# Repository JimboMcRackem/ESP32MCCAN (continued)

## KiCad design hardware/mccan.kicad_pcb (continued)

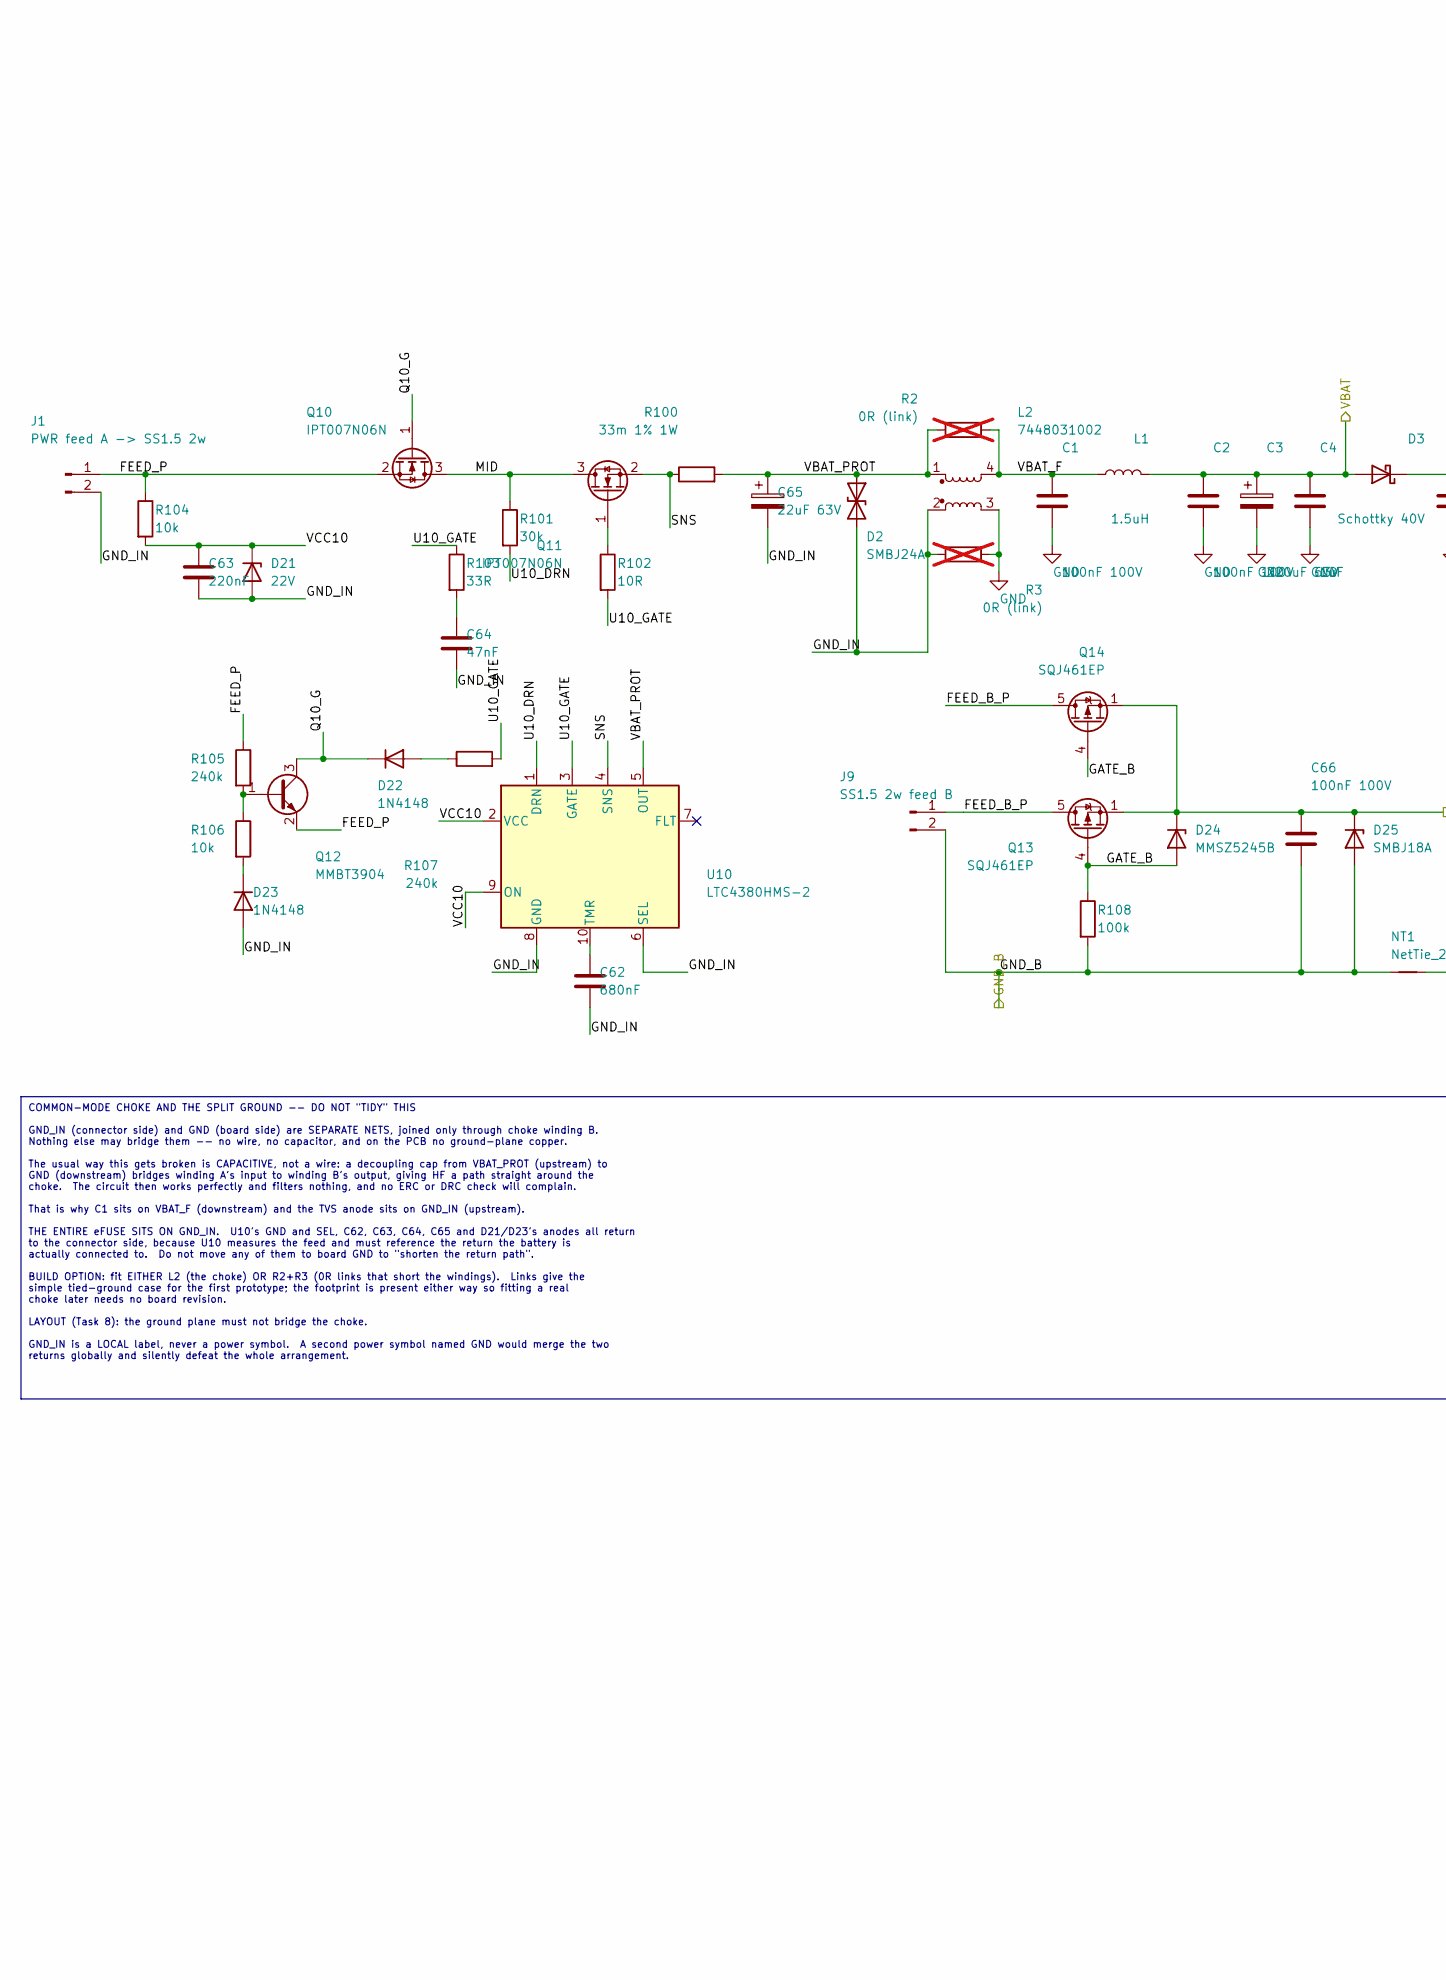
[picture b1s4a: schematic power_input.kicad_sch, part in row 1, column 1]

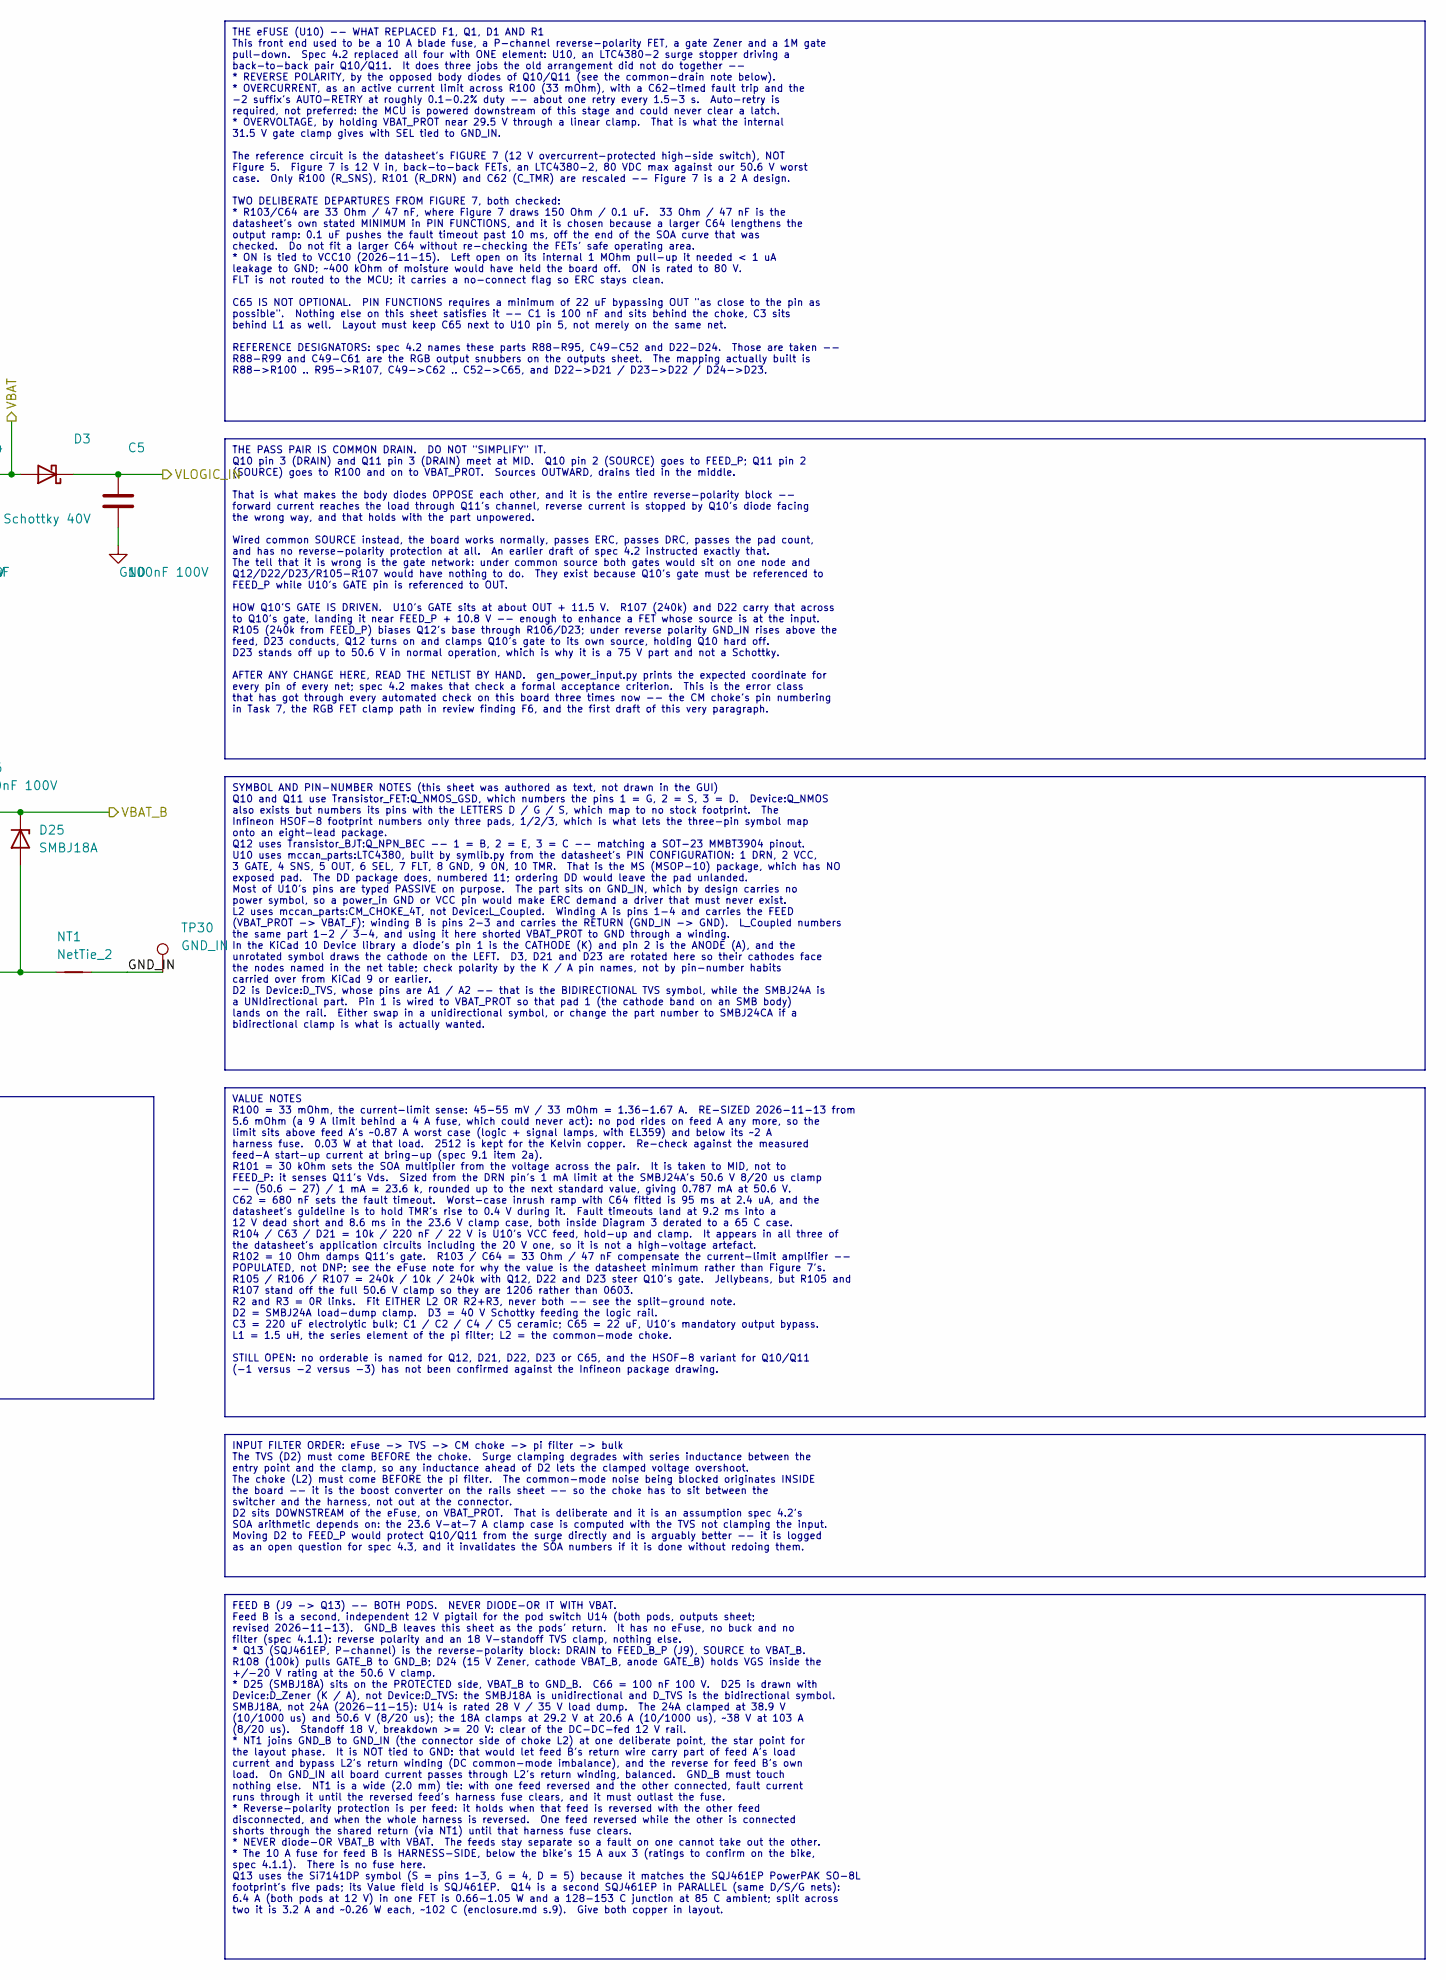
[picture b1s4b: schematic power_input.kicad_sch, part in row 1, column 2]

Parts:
C1: 100nF 100V; C_0603_1608Metric
C2, C5, C66: 100nF 100V; C_0805_2012Metric
C3: 220uF 63V; CP_Elec_10x10.5
C4: 1uF; C_1206_3216Metric
C62: 680nF; C_0603_1608Metric
C63: 220nF; C_0603_1608Metric
C64: 47nF; C_0805_2012Metric
C65: 22uF 63V; CP_Elec_6.3x7.7
D2: SMBJ24A; D_SMB
D3: Schottky 40V; D_SMA
D21: 22V; D_SOD-123
D22, D23: 1N4148; D_SOD-323
D24: MMSZ5245B; D_SOD-123
D25: SMBJ18A; D_SMB
J1: PWR feed A -> SS1.5 2w; SolderWire-1.5sqmm_1x02_P6mm_D1.7mm_OD3mm_Relief
J9: SS1.5 2w feed B; SolderWire-1.5sqmm_1x02_P6mm_D1.7mm_OD3mm_Relief
L1: 1.5uH; L_Vishay_IHLP-4040
L2: 7448031002; Wurth_WE-CMBNC_7448031002
NT1: NetTie_2; NetTie-2_SMD_Pad2.0mm
Q10, Q11: IPT007N06N; Infineon_PG-HSOF-8-1
Q12: MMBT3904; SOT-23
Q13, Q14: SQJ461EP; PowerPAK_SO-8L_Single
R2, R3: 0R (link); R_2512_6332Metric; not fitted
R100: 33m 1% 1W; R_2512_6332Metric
R101: 30k; R_1206_3216Metric
R102: 10R; R_0603_1608Metric
R103: 33R; R_0603_1608Metric
R104, R106: 10k; R_0603_1608Metric
R105, R107: 240k; R_1206_3216Metric
R108: 100k; R_0603_1608Metric
TP30: GND_IN; TestPoint_Pad_D1.5mm
U10: LTC4380HMS-2; MSOP-10_3x3mm_P0.5mm

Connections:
/GND_B: C66.2, D25.2 (A), J9.2, NT1.1, R108.2; also elsewhere on the board
/VBAT: C2.1, C3.1, C4.1, D3.2 (A), L1.2; also elsewhere on the board
/VBAT_B: C66.1, D24.1 (K), D25.1 (K), Q13.1 (S), Q13.2 (S), Q13.3 (S), Q14.1 (S), Q14.2 (S), Q14.3 (S); also elsewhere on the board
/VLOGIC_IN: C5.1, D3.1 (K); also elsewhere on the board
/power_input/FEED_B_P: J9.1, Q13.5 (D), Q14.5 (D)
/power_input/FEED_P: J1.1, Q10.2 (S), Q12.2 (E), R104.1, R105.1
/power_input/GATE_B: D24.2 (A), Q13.4 (G), Q14.4 (G), R108.1
/power_input/GND_IN: C62.2, C63.2, C64.2, C65.2, D2.2 (A2), D21.2 (A), D23.2 (A), J1.2, L2.2, NT1.2, R3.1, TP30.1, U10.6 (SEL), U10.8 (GND)
/power_input/MID: Q10.3 (D), Q11.3 (D), R101.1
/power_input/Q10_G: D22.1 (K), Q10.1 (G), Q12.3 (C)
/power_input/SNS: Q11.2 (S), R100.1, U10.4 (SNS)
/power_input/U10_DRN: R101.2, U10.1 (DRN)
/power_input/U10_GATE: R102.2, R103.1, R107.2, U10.3 (GATE)
/power_input/VBAT_F: C1.1, L1.1, L2.4, R2.2
/power_input/VBAT_PROT: C65.1, D2.1 (A1), L2.1, R2.1, R100.2, U10.5 (OUT)
/power_input/VCC10: C63.1, D21.1 (K), R104.2, U10.2 (VCC), U10.9 (ON)
GND: C1.2, C2.2, C3.2, C4.2, C5.2, L2.3, R3.2; also elsewhere on the board
unnamed: C64.1, R103.2
unnamed: D22.2 (A), R107.1
unnamed: D23.1 (K), R106.2
unnamed: Q11.1 (G), R102.1
unnamed: Q12.1 (B), R105.2, R106.1
unnamed: C62.1, U10.10 (TMR)

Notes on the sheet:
FEED B (J9 -> Q13) -- BOTH PODS. NEVER DIODE-OR IT WITH VBAT. Feed B is a second, independent 12 V pigtail for the pod switch U14 (both pods, outputs sheet; revised 2026-11-13). GND_B leaves this sheet as the pods' return. It has no eFuse, no buck and no filter (spec 4.1.1): reverse polarity and an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
INPUT FILTER ORDER: eFuse -> TVS -> CM choke -> pi filter -> bulk The TVS (D2) must come BEFORE the choke. Surge clamping degrades with series inductance between the entry point and the clamp, so any inductance ahead of D2 lets the clamped voltage overshoot. The choke (L2) must come BEFORE the pi f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
VALUE NOTES R100 = 33 mOhm, the current-limit sense: 45-55 mV / 33 mOhm = 1.36-1.67 A. RE-SIZED 2026-11-13 from 5.6 mOhm (a 9 A limit behind a 4 A fuse, which could never act): no pod rides on feed A any more, so the limit sits above feed A's ~0.87 A worst case (logic + signal lamps, with EL359) an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
THE PASS PAIR IS COMMON DRAIN. DO NOT "SIMPLIFY" IT. Q10 pin 3 (DRAIN) and Q11 pin 3 (DRAIN) meet at MID. Q10 pin 2 (SOURCE) goes to FEED_P; Q11 pin 2 (SOURCE) goes to R100 and on to VBAT_PROT. Sources OUTWARD, drains tied in the middle. That is what makes the body diodes OPPOSE each other, and it 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
THE eFUSE (U10) -- WHAT REPLACED F1, Q1, D1 AND R1 This front end used to be a 10 A blade fuse, a P-channel reverse-polarity FET, a gate Zener and a 1M gate pull-down. Spec 4.2 replaced all four with ONE element: U10, an LTC4380-2 surge stopper driving a back-to-back pair Q10/Q11. It does three job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
SYMBOL AND PIN-NUMBER NOTES (this sheet was authored as text, not drawn in the GUI) Q10 and Q11 use Transistor_FET:Q_NMOS_GSD, which numbers the pins 1 = G, 2 = S, 3 = D. Device:Q_NMOS also exists but numbers its pins with the LETTERS D / G / S, which map to no stock footprint. The Infineon HSOF-8 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
COMMON-MODE CHOKE AND THE SPLIT GROUND -- DO NOT "TIDY" THIS GND_IN (connector side) and GND (board side) are SEPARATE NETS, joined only through choke winding B. Nothing else may bridge them -- no wire, no capacitor, and on the PCB no ground-plane copper. The usual way this gets broken is CAPACITIV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

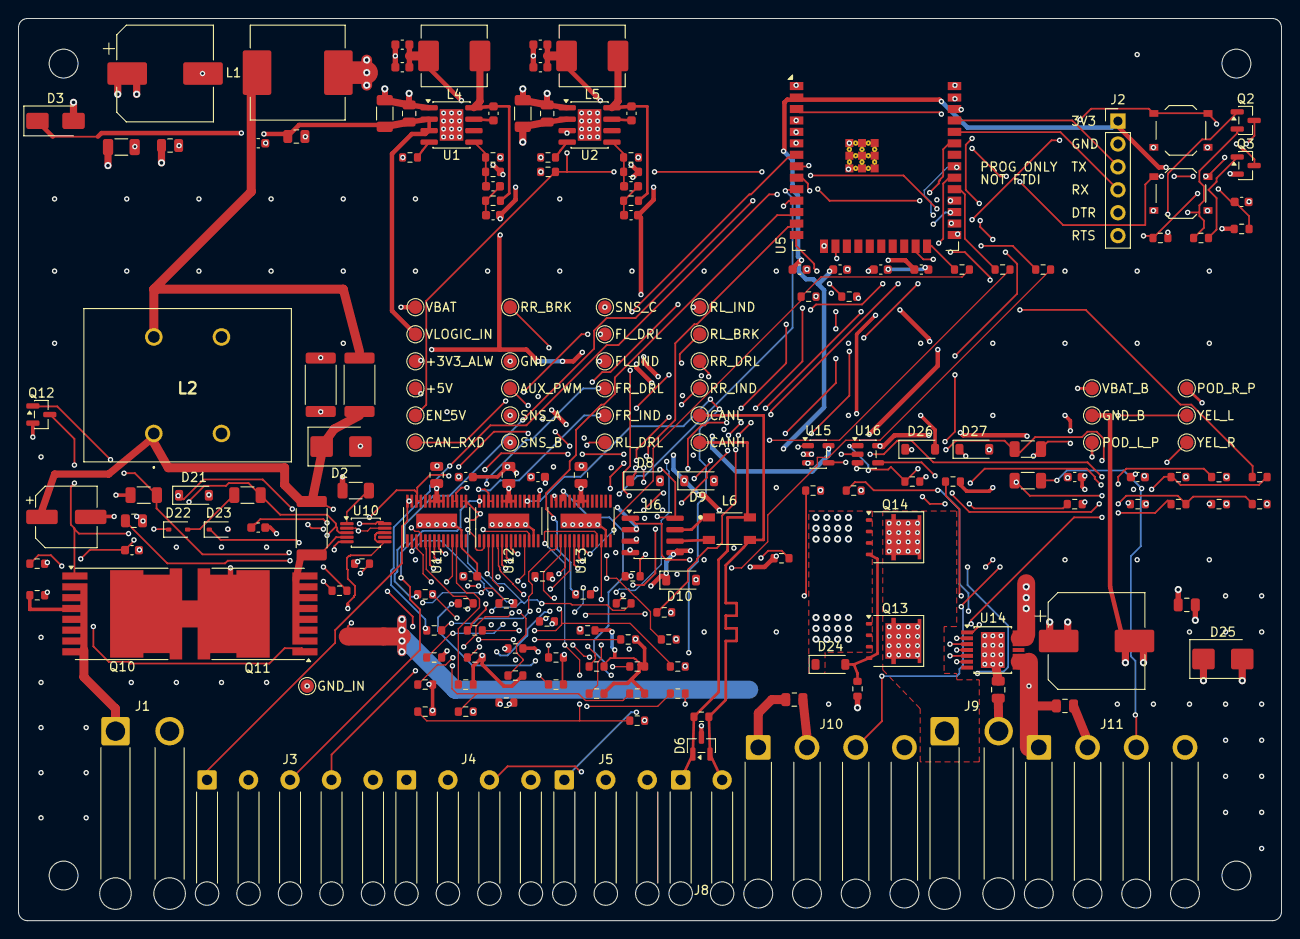
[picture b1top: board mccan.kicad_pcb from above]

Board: 8 copper layers, 140.0 x 100.0 mm, 199 parts (0 on the bottom side), 115 nets.

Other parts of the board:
H1, H2, H3, H4: MountingHole; MountingHole_3.2mm_M3

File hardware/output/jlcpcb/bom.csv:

Comment,Designator,Footprint,LCSC
1.2k,R80,R_0603_1608Metric,C22765
1.5uH,L1,L_Vishay_IHLP-4040,C845071
100k,"R19,R86,R87,R108",R_0603_1608Metric,C25803
100nF 100V,C1,C_0603_1608Metric,C15725
100nF 100V,"C2,C5,C7,C13,C41,C42,C43,C66,C67",C_0805_2012Metric,C28233
100nF,"C17,C36,C38,C39,C71,C72",C_0603_1608Metric,C14663
10R,R102,R_0603_1608Metric,C22859
10k,"R22,R24,R25,R28,R29,R36,R104,R106",R_0603_1608Metric,C25804
10nF 100V,"C69,C70",C_0805_2012Metric,C18741
10nF,"C44,C45,C46",C_0603_1608Metric,C57112
10uF,C35,C_0603_1608Metric,C19702
133k,R17,R_0603_1608Metric,C22870
174k,R18,R_0603_1608Metric,C22890
1N4148,"D22,D23",D_SOD-323,C2128
1uF,C37,C_0603_1608Metric,C15849
1uF,C4,C_1206_3216Metric,C13832
2.2nF,"C8,C14,C28,C29",C_0603_1608Metric,C1604
2.2uF,"C6,C12",C_1206_3216Metric,C170101
20.5k,R4,R_0603_1608Metric,C22910
200k,"R6,R9",R_0603_1608Metric,C25811
220nF,C63,C_0603_1608Metric,C107083
220uF 63V,"C3,C68",CP_Elec_10x10.5,C56151978
220,"R84,R85",R_1206_3216Metric,C17957
22V,D21,D_SOD-123,C2108
22uF 63V,C65,CP_Elec_6.3x7.7,C72501
22uF,"C10,C11,C16",C_0603_1608Metric,C86295
240k,"R105,R107",R_1206_3216Metric,C18001
30k,R101,R_1206_3216Metric,C17999
31.6k,R7,R_0603_1608Metric,C25967
330,"R82,R83",R_0603_1608Metric,C23138
33R,R103,R_0603_1608Metric,C23140
33m 1% 1W,R100,R_2512_6332Metric,C2985721
348k,R5,R_0603_1608Metric,C23006
39pF,C15,C_0603_1608Metric,C1666
4.7k,"R30,R31,R32,R40,R41,R42,R43,R44,R45,R46,R47,R48,R49,R71,R72,R73,R76,R77",R_0603_1608Metric,C23162
47k,"R33,R50,R51,R52,R53,R54,R55,R56,R57,R58,R59,R60,R61,R74,R75,R78,R79,R81",R_0603_1608Metric,C25819
47nF,C64,C_0805_2012Metric,C17074
5.11k,"R68,R69,R70",R_0603_1608Metric,C23067
56.2k,"R62,R63,R64",R_0603_1608Metric,C23080
634k,R8,R_0603_1608Metric,C65831
680nF,C62,C_0603_1608Metric,C107067
68pF,C9,C_0603_1608Metric,C28262
7448031002,L2,Wurth_WE-CMBNC_7448031002,C1519839
74AHCT1G126GV,"U15,U16",SOT-23-5,C52140416
ACT45B-510-2P-TL003,L6,TDK_ACT45B,C76584
BAT54,"D8,D9,D10",D_SOD-123,C699107
BOOT,SW1,SW_Push_1P1T_XKB_TS-1187A,C318884
BTS7008-2EPA,U14,Infineon_PG-TSDSO-14-22,C534830
BZT52C5V6,"D26,D27",D_SOD-123,C2119
EN/RESET,SW2,SW_Push_1P1T_XKB_TS-1187A,C318884
ESP32-WROOM-32E-N8,U5,ESP32-WROOM-32E,C701342
IPT007N06N,"Q10,Q11",Infineon_PG-HSOF-8-1,C122552
LM5164QDDARQ1,"U1,U2",SOIC-8-1EP_3.9x4.9mm_P1.27mm_EP2.62x3.51mm,C2072225
LTC4380HMS-2,U10,MSOP-10_3x3mm_P0.5mm,C688451
MDA7030-220M,"L4,L5",L_KOHERelec_MDA7030,C2847487
MMBT3904,"Q2,Q3,Q12",SOT-23,C20526
MMSZ5245B,D24,D_SOD-123,C2126
PESD2CANFD24LT-Q,D6,SOT-23,C6952426
Prog/UART,J2,PinHeader_1x06_P2.54mm_Vertical,C492405
SMBJ18A,D25,D_SMB,C168805
SMBJ24A,D2,D_SMB,C123819
SQJ461EP,"Q13,Q14",PowerPAK_SO-8L_Single,C3279500
Schottky 40V,D3,D_SMA,C2480
TJA1042T/3,U6,SOIC-8_3.9x4.9mm_P1.27mm,C132227
TPS4HC120AQDGQRQ1,"U11,U12,U13",TI_DGQ0028C,C44545560

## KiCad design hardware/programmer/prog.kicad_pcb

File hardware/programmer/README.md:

# MCCAN programmer board (rev A)

A bench programmer for the MCCAN board's J2 header: USB-C in, J2's six signals out.
It does for the MCCAN board what the USB chip on an ESP32 dev board does: one cable from the
laptop, `py -3.13 -m platformio run -t upload`, no buttons, no bench supply.

Spec: `docs/superpowers/specs/2026-11-14-programmer-board-design.md`.
Plan: `docs/superpowers/plans/2026-11-14-programmer-board.md`.

## What it does

- **USB-C device** (CC1/CC2 5.1 kΩ to GND, default USB power, no PD) into a **CH343P**, a USB
  CDC-ACM serial chip that Windows runs with its built-in driver: nothing to install.
- **Powers the MCCAN board's 3.3 V rail** (`+3V3_ALW`, J2 pin 1) from USB: VBUS → AMS1117-3.3 →
  LM66100 ideal diode → J2 pin 1. ≥ 600 mA. The ideal diode stops any current flowing back
  into the programmer when the MCCAN board's own supply is up; the two then share the load.
  Only the 3.3 V rail is powered: lights, pod outputs and CAN stay dead on the bench.
  **Plug it into a laptop port directly, not through a hub:** at a full 600 mA from a 4.75 V
  port through a 1 m cable, the AMS1117 is in dropout and the MCCAN rail is 3.03 V (ESP32
  minimum 3.0 V); a bus-powered hub's 4.4 V would take it below. 600 mA is also above USB 2.0's
  500 mA default; the ESP32's real average draw (~200–300 mA) is well inside both.
- **TX/RX crossed on the board**, so the cable is straight-through, pin 1 to pin 1.
- **DTR and RTS are crossed on the board** (CH343 ~DTR → header pin 6 RTS, ~RTS → pin 5 DTR).
  The MCCAN board's EN transistor Q2 has its emitter on DTR and its base fed from RTS, the
  reverse of Espressif's dev-board circuit, so esptool's reset reaches EN only through the
  swap. `check_netlist_prog` traces esptool's two steps through both boards' netlists.
  *Consequence for the main board:* any other USB-serial adapter on J2 also needs DTR and RTS
  swapped (adapter DTR → J2.6, RTS → J2.5). The main board's notes (`bring-up.md`,
  `part-selection.md`, `enclosure.md`, the schematic note from `gen_mcu_can.py`) say so.
- **DTR/RTS** go through a 74LVC2G125 buffer powered from USB, whose I_off outputs go
  high-impedance when it is unpowered, so an unplugged programmer leaves the auto-reset pair
  alone. **R10 (1k) bleeds +3V3_USB**: with USB unplugged, the ESP's TX back-feeds that rail
  through the CH343's RXD ESD diode, and without a load it would rise to ~2 V and wake U5.
- **Series resistors** on every signal, so a reversed cable damages nothing.
- **LEDs:** PWR (3.3 V output present), TX and RX activity.

J2 pinout, printed on the silk beside the header (pin 1 marked by an arrow):

| Pin | 1 | 2 | 3 | 4 | 5 | 6 |
|---|---|---|---|---|---|---|
| Net | 3V3 | GND | TX (ESP32 transmits) | RX (ESP32 receives) | DTR | RTS |

## Regenerate and gate

Everything here is generated; never hand-edit `.kicad_sch`, `.kicad_pcb`, `.kicad_pro` or
`.kicad_dru`. From `hardware/programmer/`:

```bash
python scripts/gen_sch.py                     # schematic (then export the netlist, below)
"C:/Program Files/KiCad/10.0/bin/kicad-cli.exe" sch export netlist --format kicadsexpr \
    -o output/netlist.net prog.kicad_sch
python scripts/gen_pcb.py                     # board, ~35 s (deterministic router)
python scripts/gen_fab_prog.py                # output/jlcpcb/ (runs DRC first, refuses if dirty)
bash scripts/gate.sh                          # every gate; exit 0 only if all PASS
```

`gate.sh` prints one row per gate: `test_parts`, `test_netlist_prog`, `test_board`,
`test_fab_prog`, `erc` (and the committed netlist matches the schematic), `check_netlist_prog`
(J2 pinout, crossover, power and back-feed budgets), `drc` (0 violations, 0 unconnected,
0 parity, all severities), `check_board` (geometry DRC does not check), `fab_check`, `stock`
(5 boards, JLCPCB's own stock; needs the network).

## Budgets (from `check_netlist_prog.budget()`)

| Quantity | Value | Meaning |
|---|---|---|
| `v_u3_out_min` | 3.206 V | U3 output at 600 mA: the lower of its −2 % regulation and 4.75 V VBUS − 1 m USB cable − 1.3 V max dropout |
| `v_at_mccan_min` | 3.029 V | rail at the MCCAN board: `v_u3_out_min` less the LM66100 and jumper-cable drops (ESP32 min 3.0 V) |
| `u3_watts` | 1.23 W | AMS1117 dissipation at 600 mA from 5.25 V |
| `u3_tj_c` | 111.1 °C | U3 junction at a 25 °C bench, θ 70 °C/W on the 200 mm² heatsink pour (limit 125 °C) |
| `misplug_ma` | R3 0.71, R4 7.11, R5 12.37, R6 12.37 mA | worst current through each series resistor with the cable reversed |
| `rxd_backfeed_ma` | 0.604 mA | ESP32 TX back into the unpowered CH343P's RXD |
| `usb_rail_backfed_v` | 0.604 V | +3V3_USB with USB unplugged, that current into the R10 bleeder alone (U5 needs 1.65 V to wake) |
| `en_hold_v` | 3.24 V | MCCAN EN with the programmer attached and unpowered (U5 Ioff leakage only) |

## Decided here

| Decision | Why |
|---|---|
| CH343P (C2846043), fallback CH9102F (C2858418) | CDC-ACM: no driver install (spec 6.5) |
| AMS1117-3.3 + LM66100 ideal diode | ≥ 600 mA; no back-current when both boards are powered (spec 6.3) |
| SN74LVC2G125 on DTR/RTS | an unpowered CH343's I/O pins are not high-impedance; the buffer's I_off outputs are |
| DTR/RTS crossed on the programmer, not on the MCCAN board | the MCCAN board is merged and DRC-clean (spec 4: no change to it); the auto-reset trace gate fails if either side changes |
| R10 1k bleeder on +3V3_USB | keeps the back-fed rail at 0.6 V so U5 stays off (costs 3.3 mA from USB) |
| AMS1117 kept, with the laptop-port warning above | 3.03 V worst case still meets the ESP32's 3.0 V; a low-dropout part would mean a new part and layout for a bench-only corner |
| USBLC6-2SC6 on D+/D− | USB ESD (spec 6.7) |
| R3 4.7k in ESP32 TX → CH343 RXD, R4 470 in CH343 TXD → ESP32 RX, R5/R6 270 on DTR/RTS | misplug and back-feed currents above; 270 not 220 keeps DTR/RTS ≤ 15 mA |
| PWR LED yellow-green KT-0603YG (C2289), RX LED yellow KT-0603Y (C2287) | the planned green/yellow were out of stock; pure green's 3.1 V Vf is too high for 3.3 V through 1k |
| 2 layers, 20 × 40 mm, all parts top | spec 6.7 |
| GND poured both sides; +3V3_USB heatsink 200 mm² on F+B with six thermal vias | U3's 1.23 W |
| USB pair hand-routed; other nets by an in-repo deterministic grid router | the router's output is graded by DRC and `check_board.py` like any copper |
| Power tracks 0.5 mm, necking to 0.3 mm only within 1.5 mm of a fine-pitch pin | `check_board.thin_power_tracks` |
| USB pair: ≤ 2 vias per line, skew ≤ 5 mm, length ≤ 30 mm (actual 19.2 / 22.4 mm) | full-speed USB (12 Mb/s, ≥ 4 ns edges): 3 mm of skew is ~20 ps |
| References on F.Fab; silk carries J2 net names, LED functions, "MCCAN PROG A" | spec 6.7 labels by function; `assembly.pdf` carries the references |
| DRU: J1 land pattern 0.12 mm; J1 silk may meet the edge; one thermal spoke allowed | the receptacle's pads and mouth are fixed by the part; C6/C7 GND pads each have their own via |
| CPL places J1 and J2 at their pad centres | KiCad's origin for both is not the body centre JLCPCB expects |

Every ruling made while building it, with what it costs if wrong, is in the branch's history
and the final report on the branch.

## Ordering (with the MCCAN boards, spec 10)

Upload `output/jlcpcb/gerbers.zip`, `bom.csv` and `cpl.csv` **in the same JLCPCB order as the
MCCAN boards** — the MCCAN order waits for this board.

- **5 pcs, 2 layers, 1.6 mm FR-4**, green mask, HASL or ENIG.
- **PCB assembly: standard, top side.** Add the **through-hole service for J2** (the 1×6 header).
- **Check EVERY row of `output/jlcpcb/rotation-review.txt` in JLCPCB's placement preview**
  before paying. No rotation offset has been checked against JLCPCB: U1–U5 pin 1, D1–D3 cathode
  (towards J1), J1 and J2 on their pads.
- **Re-run the stock check the day the order is placed:**
  `python scripts/check_stock_prog.py --boards 5` (the copy in `output/jlcpcb/stock.txt` is
  from when the package was cut).
- Read JLCPCB's DFM report before paying.

## Buy separately (spec 7)

- A **6-way female-to-female 2.54 mm jumper cable, straight-through, 10–20 cm**. Buy spares.
- A **USB-C cable** (data, not charge-only).

## Bench acceptance (when the boards arrive)

- [ ] USB only: the PWR LED lights, and the laptop sees a serial port with no driver install.
- [ ] Programmer on an MCCAN board, USB only: `py -3.13 -m platformio run -t upload` flashes
      with no button presses; the serial monitor shows the boot log; the WiFi access point
      appears.
- [ ] MCCAN board on its bench supply, programmer plugged in: no current flows back into the
      programmer (measure at its output; it may be supplying part of the load), the rail stays
      between 3.2 and 3.4 V, and flashing still works.
- [ ] Cable reversed at one end, USB connected, for 10 s: neither board is damaged; the ESP32
      is held in reset; with the cable put right, the flashing step passes again.
- [ ] Output shorted to ground for 10 s: the programmer recovers when the short is removed.
- [ ] Programmer attached, **USB unplugged**, MCCAN board on its bench supply: the ESP32 keeps
      running (no reset): plug USB back in and the serial log carries on with no new boot
      banner.

## First flash: install the real OTA key

The firmware's OTA public key (`src/domain/update_pubkey.h`) is still the all-zero
placeholder, so OTA refuses every update until a keyed build is flashed over J2. Make the
first flash over this programmer a build with the real key: run
`python tools/sign_update.py keygen`, keep the private key safe (not in git), build, and
upload over J2. After that, J2 is the recovery path when OTA cannot be used.

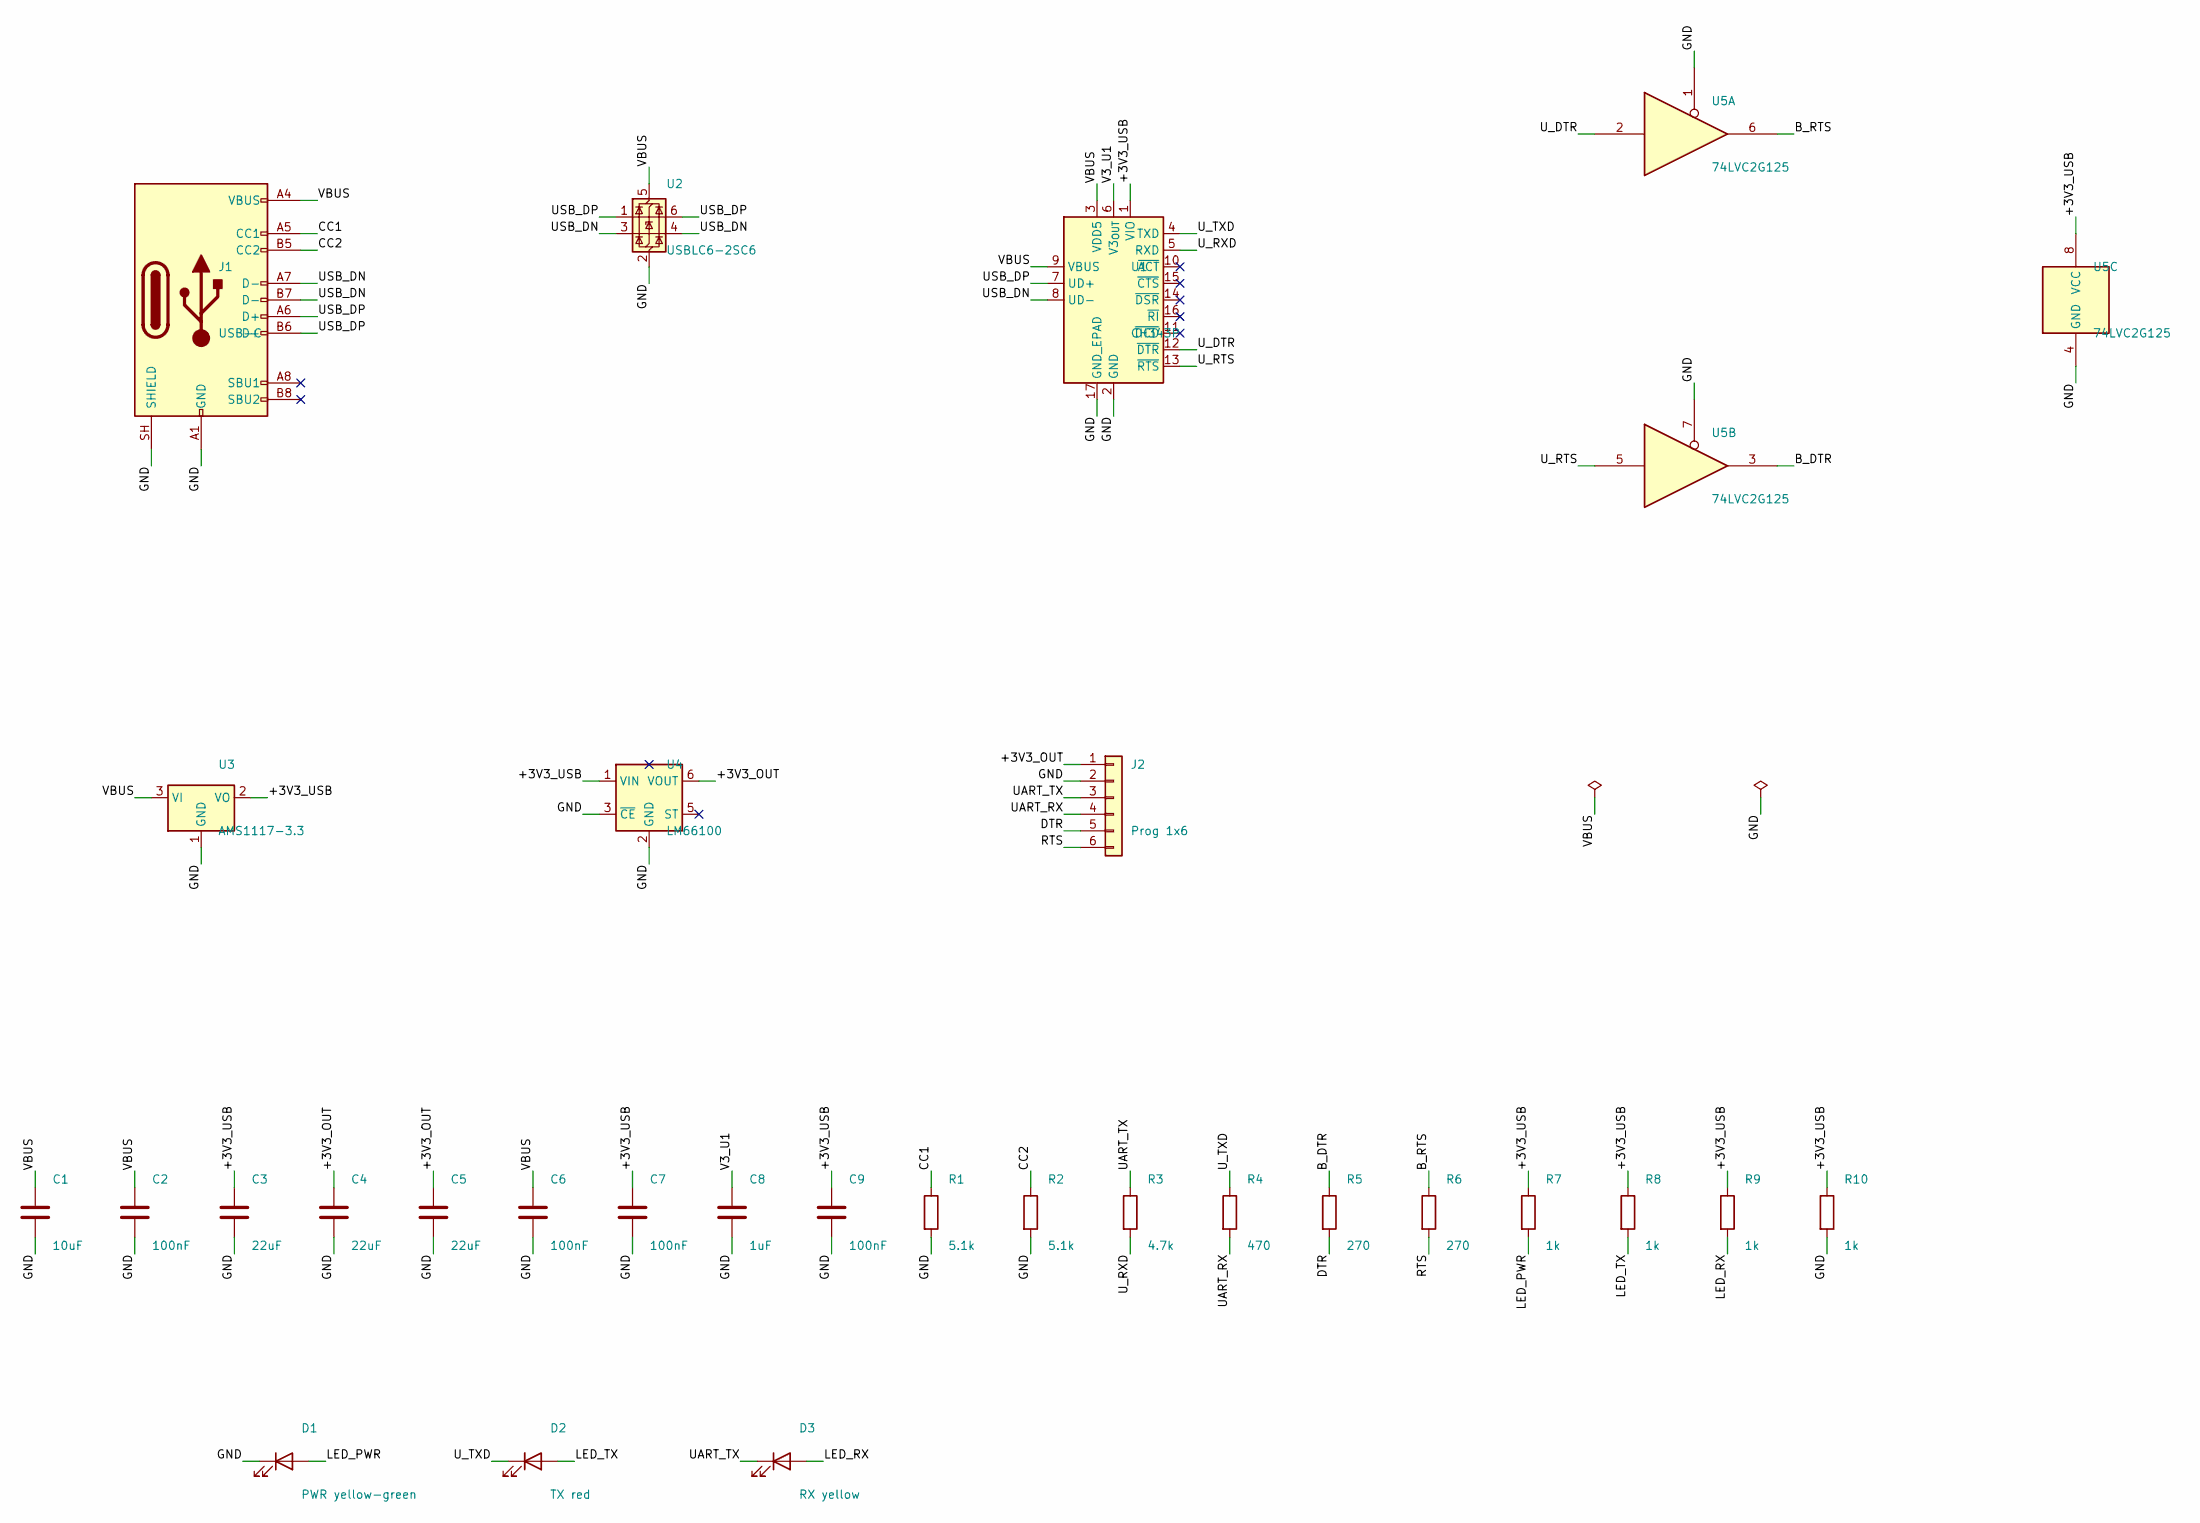
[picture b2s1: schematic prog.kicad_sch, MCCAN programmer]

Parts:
C1: 10uF; C_0805_2012Metric; MPN CL21A106KAYNNNE; LCSC C15850
C2, C6, C7, C9: 100nF; C_0603_1608Metric; MPN CC0603KRX7R9BB104; LCSC C14663
C3, C4, C5: 22uF; C_0805_2012Metric; MPN CL21A226MAQNNNE; LCSC C45783
C8: 1uF; C_0603_1608Metric; MPN CL10A105KB8NNNC; LCSC C15849
D1: PWR yellow-green; LED_0603_1608Metric; MPN KT-0603YG; LCSC C2289
D2: TX red; LED_0603_1608Metric; MPN KT-0603R; LCSC C2286
D3: RX yellow; LED_0603_1608Metric; MPN KT-0603Y; LCSC C2287
J1: USB-C; USB_C_Receptacle_HRO_TYPE-C-31-M-12; MPN TYPE-C-31-M-12; LCSC C165948
J2: Prog 1x6; PinHeader_1x06_P2.54mm_Vertical; MPN PZ254V-11-06P; LCSC C492405
R1, R2: 5.1k; R_0603_1608Metric; MPN 0603WAF5101T5E; LCSC C23186
R3: 4.7k; R_0603_1608Metric; MPN 0603WAF4701T5E; LCSC C23162
R4: 470; R_0603_1608Metric; MPN 0603WAF4700T5E; LCSC C23179
R5, R6: 270; R_0603_1608Metric; MPN 0603WAF2700T5E; LCSC C22966
R7, R8, R9, R10: 1k; R_0603_1608Metric; MPN 0603WAF1001T5E; LCSC C21190
U1: CH343P; WCH_QFN-16-1EP_3x3mm_P0.5mm_EP1.8x1.8mm; MPN CH343P; LCSC C2846043
U2: USBLC6-2SC6; SOT-23-6; MPN USBLC6-2SC6; LCSC C7519
U3: AMS1117-3.3; SOT-223-3_TabPin2; MPN AMS1117-3.3; LCSC C6186
U4: LM66100; SOT-363_SC-70-6; MPN LM66100DCKR; LCSC C2869734
U5: 74LVC2G125; SSOP-8_2.95x2.8mm_P0.65mm; MPN SN74LVC2G125DCTR; LCSC C206035

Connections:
/+3V3_OUT: C4.1, C5.1, J2.1, U4.6 (VOUT)
/+3V3_USB: C3.1, C7.1, C9.1, R7.1, R8.1, R9.1, R10.1, U1.1 (VIO), U3.2 (VO), U4.1 (VIN), U5.8 (VCC)
/B_DTR: R5.1, U5.3
/B_RTS: R6.1, U5.6
/CC1: J1.A5 (CC1), R1.1
/CC2: J1.B5 (CC2), R2.1
/DTR: J2.5, R5.2
/GND: C1.2, C2.2, C3.2, C4.2, C5.2, C6.2, C7.2, C8.2, C9.2, D1.1 (K), J1.A1 (GND), J1.A12 (GND), J1.B1 (GND), J1.B12 (GND), J1.SH (SHIELD), J2.2, R1.2, R2.2, R10.2, U1.2 (GND), U1.17 (GND_EPAD), U2.2 (GND), U3.1 (GND), U4.2 (GND), U4.3 (~CE), U5.1, U5.4 (GND), U5.7
/LED_PWR: D1.2 (A), R7.2
/LED_RX: D3.2 (A), R9.2
/LED_TX: D2.2 (A), R8.2
/RTS: J2.6, R6.2
/UART_RX: J2.4, R4.2
/UART_TX: D3.1 (K), J2.3, R3.1
/USB_DN: J1.A7 (D-), J1.B7 (D-), U1.8 (UD-), U2.3 (I/O2), U2.4 (I/O2)
/USB_DP: J1.A6 (D+), J1.B6 (D+), U1.7 (UD+), U2.1 (I/O1), U2.6 (I/O1)
/U_DTR: U1.12 (~DTR), U5.2
/U_RTS: U1.13 (~RTS), U5.5
/U_RXD: R3.2, U1.5 (RXD)
/U_TXD: D2.1 (K), R4.1, U1.4 (TXD)
/V3_U1: C8.1, U1.6 (V3_{OUT})
/VBUS: C1.1, C2.1, C6.1, J1.A4 (VBUS), J1.A9 (VBUS), J1.B4 (VBUS), J1.B9 (VBUS), U1.3 (VDD5), U1.9 (VBUS), U2.5 (VBUS), U3.3 (VI)

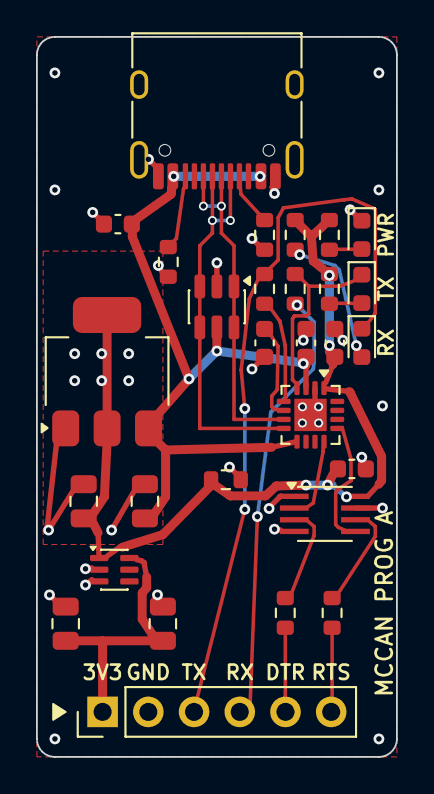
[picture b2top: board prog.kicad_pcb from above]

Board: 2 copper layers, 20.0 x 40.0 mm, 29 parts (0 on the bottom side), 22 nets.

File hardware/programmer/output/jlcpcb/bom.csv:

Comment,Designator,Footprint,LCSC
10uF,C1,C_0805_2012Metric,C15850
100nF,"C2,C6,C7,C9",C_0603_1608Metric,C14663
22uF,"C3,C4,C5",C_0805_2012Metric,C45783
1uF,C8,C_0603_1608Metric,C15849
PWR yellow-green,D1,LED_0603_1608Metric,C2289
TX red,D2,LED_0603_1608Metric,C2286
RX yellow,D3,LED_0603_1608Metric,C2287
USB-C,J1,USB_C_Receptacle_HRO_TYPE-C-31-M-12,C165948
Prog 1x6,J2,PinHeader_1x06_P2.54mm_Vertical,C492405
5.1k,"R1,R2",R_0603_1608Metric,C23186
4.7k,R3,R_0603_1608Metric,C23162
470,R4,R_0603_1608Metric,C23179
270,"R5,R6",R_0603_1608Metric,C22966
1k,"R7,R8,R9,R10",R_0603_1608Metric,C21190
CH343P,U1,WCH_QFN-16-1EP_3x3mm_P0.5mm_EP1.8x1.8mm,C2846043
USBLC6-2SC6,U2,SOT-23-6,C7519
AMS1117-3.3,U3,SOT-223-3_TabPin2,C6186
LM66100,U4,SOT-363_SC-70-6,C2869734
74LVC2G125,U5,SSOP-8_2.95x2.8mm_P0.65mm,C206035

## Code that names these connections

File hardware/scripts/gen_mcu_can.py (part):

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
ESP32-WROOM-32E-N8 on the plan4 pin map (twelve outputs, shared diagnostics, three sense
inputs), TJA1042T/3 with hardware-enforced listen-only, programming header with auto-reset.
GPIO 13 (pad 16) is AUX_PWM, the left pod's yellow PWM (aux stage, 2026-11-13); it was the
status LED, D5, which is gone.  GPIO 12 (pad 14) is AUX_PWM_R, the right pod's yellow PWM
(2026-11-21, so the pods can be dimmed separately); R36 still holds it low at reset.
"""
import os, re, sys, uuid
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
# --- shared diagnostic lines (R1): U5 pad -> 4.7k series -> *_Q to the outputs sheet.  One
#     series resistor per shared line, at the MCU (TI TPS4H160 7.3.7.5).  The 47k pull-down
#     sits on DIAG_EN_Q, chip side: GPIO2 must be low for download and the chips' DIAG_EN
#     must be defined.  DIAG_SEL0/1 get no pull (GPIO5/15 strapping, harmless while DIAG_EN low).
RX = round(U5["24"][0] + 25.4, 4)                   # series resistors start here, clear of labels
for ref, pnum, net in (("R30", "24", "DIAG_EN"), ("R31", "29", "DIAG_SEL0"),
                       ("R32", "23", "DIAG_SEL1")):
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L6 = place("L6", "mccan_parts:CM_CHOKE_4T", "ACT45B-510-2P-TL003", 284.48, 95.25, 0, COUPLED,
           [("Reference", "L6", 284.48, 88.9, 0), ("Value", "ACT45B-510-2P-TL003", 284.48, 101.6, 0)],
           desc="Coupled inductor, common-mode choke")
# CANH enters winding A at pin 1 and leaves at pin 4; CANL enters winding B at pin 2 and
# leaves at pin 3.  Geometrically identical to before -- only the pin numbers changed.
w(U6["7"], L6["1"])
w(U6["6"], L6["2"])
# ONE dual-line protector, not two discretes.  The Nexperia PESD2CANFD24U-T is a single
# SOT23 holding both bidirectional elements: pin 1 (K1) on CANH, pin 2 (K2) on CANL,
# pin 3 (CC) the common node to GND.  Replaced the placeholder D6/D7 pair on 2026-09-19;
# `part-selection.md` records why a single dual-line part is preferred over two discretes.
# VRWM 24 V, VCL 33 V typ at 1 A (8/20 us), Cd 3.5 pF, AEC-Q101.
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# (datasheet 19 July 2022, Table 2: 1 K1, 2 K2, 3 CC), VRWM 24 V, Cd 10 pF, AEC-Q101; the
# symbol keeps its PESD2CANFD24U name -- only the value changed.
#
# The two protected pins land exactly on the CANH and CANL runs, so each run is drawn as
# TWO segments meeting AT the pin rather than one segment the pin happens to touch.  A
# pin sitting mid-wire does connect, but this sheet has already produced one silent
# connectivity defect of that shape, so the pin is made a wire endpoint and junctioned.
PESD = {"1": (-7.62, 2.54), "2": (-7.62, -2.54), "3": (0.0, -10.16)}
D6 = place("D6", "mccan_parts:PESD2CANFD24U", "PESD2CANFD24LT-Q", 302.26, 95.25, 0, PESD,
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
# ================================================================ BLOCK F: passive defaults
# R36 is a boot requirement: GPIO 12 (MTDI) selects the flash voltage when sampled at reset.
# GPIO 12 is also AUX_PWM_R (right pod yellow), so R36 is that buffer input's pull-down too.  (R30-R33, the diagnostic parts, sit in block A beside their pads.)
w((132.08, 215.9), (132.08, 220.98)); lab("AUX_PWM_R", 132.08, 215.9, 90)
a, b = vpart("R36", "Device:R", "10k", 132.08, 220.98); gnd(*b)

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note("""|ACCEPTANCE (spec 7, 8.1)
- ESP32-WROOM-32E-N8 (8 MB).  NOT the 4 MB variant, NOT the -32UE (U.FL) variant.
- Module powered from +3V3_ALW so it stays up in sleep.
- Pin assignment EXACTLY per the plan4 pin map (D2): twelve OUT_* lamp outputs, EN_5V,
  three shared diagnostic lines, SNS_A/B/C on ADC1 (GPIO 34/36/39, input-only).
- CAN_RXD on GPIO 35 (RTC-capable, EXT0 wake).  Ignition sense is gone (spec 6.2).
- CAN_STB on GPIO 14, PULLED UP to VIO (floating = standby).
- TJA1042T/3 TXD has NO connection to any GPIO; it is only pulled up to VIO.
- NO 120 ohm terminator populated; unpopulated footprint present.
- CAN common-mode choke + ESD protection on CANH/CANL.
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monitor - which asserts one line on open - from dropping the board into the bootloader.""",
"""J2's DTR/RTS are named for this circuit, NOT for a USB-UART adapter: Q2 (EN) has its
emitter on DTR, the reverse of Espressif's dev boards.  esptool's reset step drives the
adapter's DTR pin high and RTS pin low (modem lines are active low), which here would pull
IO0, not EN.  So wire adapter DTR -> J2.6 "RTS" and adapter RTS -> J2.5 "DTR".  The MCCAN
programmer board crosses them on its own copper; any other adapter needs the swap.""")

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DIAG_EN, DIAG_SEL0 and DIAG_SEL1 are shared by all three quad switches.  Each leaves the
module through its own 4.7k series resistor (R30-R32, one per shared line, not per chip) and
continues as DIAG_EN_Q / DIAG_SEL0_Q / DIAG_SEL1_Q to the outputs sheet.""",
"""R33 pulls DIAG_EN_Q low (10k, chip side).  GPIO 2 is a strapping pin that must be low for
download, and the pull-down serves both that and the switches' DIAG_EN input.  DIAG_SEL0 and
DIAG_SEL1 have NO pull: their level is irrelevant while DIAG_EN is low, and a pull-down on
GPIO 15 would mute the boot ROM log.""")

note("""|R36 ON AUX_PWM_R (GPIO 12) IS A BOOT REQUIREMENT
GPIO 12 (MTDI) selects the flash voltage at boot.  Sampled high it selects 1.8 V, which will
not run the module's 3.3 V flash.  Most WROOM-32E parts ship with the eFuse already burned so
the strap is ignored, but that is not guaranteed across date codes.  It draws no current in
sleep.""",
"""GPIO 12 also carries AUX_PWM_R, the right pod's yellow PWM, to U16 on the outputs sheet.
Firmware must leave it LOW through reset and attach its LEDC channel only after the CAN driver
has started (TWAI names GPIO 12 as its unused TX pin).  R36 is the buffer input's pull-down.""")

note("""|EN_5V PULL-DOWN IS ON THE RAILS SHEET, NOT HERE
EN_5V (GPIO 4) is pulled down by R19 next to the converter it gates, so the enable stays
defined even if the inter-sheet net is open.  One resistor per net; do not add a second.""")

# ================================================================ emit
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
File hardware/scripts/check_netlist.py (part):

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    for ref, pins in sorted(nl.part_pins.items()):
        nets = set(pins.values())
        if "VBAT" in nets and "VBAT_B" in nets:
            f.append("%s has pins on both VBAT and VBAT_B (re-merges the two feeds)" % ref)
    return f


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    en = [x for x in m
          if _func_name(nl.pinfunc.get(tuple(x.split(".", 1)), "")).startswith("EN/UVLO")]
    if not en:
        f.append("EN_5V does not reach a buck EN/UVLO pin")
    if not resistors_between(nl, "EN_5V", "GND"):
        f.append("EN_5V has no resistor to GND (enable nets carry an external pull-down)")
    return f
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    # AUX_PWM_R, so nothing on the net may pull it up.
    f = []
    if not resistors_between(nl, "AUX_PWM_R", "GND"):
        f.append("AUX_PWM_R (GPIO 12 strap) has no resistor to GND")
    for r, o in resistors_on(nl, "AUX_PWM_R"):
        if o in SUPPLIES:
            f.append("AUX_PWM_R (GPIO 12 strap) has pull-up %s to %s" % (r, o))
    return f


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                f.append("%s has no pull-down to GND (yellow must idle low)" % clamp[0])
            if not resistors_between(nl, clamp[0], yel):
                f.append("%s does not reach %s through a series resistor" % (clamp[0], yel))
    for pin, net in (("15", "VBAT_B"), ("1", "GND")):
        f += expect_pin(nl, "U14", pin, net)
    for pin in ("3", "5"):                               # DEN, DSEL: diagnosis off, defined
        n = nl.net_of("U14", pin)
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        if not is_open(nl, "U14", pin):
            f.append("U14.%s is n.c. but sits on %s" % (pin, nl.net_of("U14", pin)))
    if not resistors_between(nl, "AUX_PWM", "GND"):
        f.append("AUX_PWM has no pull-down to GND (GPIO 13 floats at reset)")
    for net in ("VBAT_B", "POD_L_P", "POD_R_P", "YEL_L", "YEL_R"):
        if any(m.split(".")[0] == "U5" for m in members(nl, net)):
            f.append("%s touches the ESP32 directly" % net)
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    for ref, (sns, _) in CHIPS.items():
        if not has_part(nl, ref):
            continue
        pad = PINS["SNS"][0]
        n = nl.net_of(ref, pad)
        tag = "%s SNS (pad %s)" % (ref, pad)
        if n is None or n.startswith("unconnected-"):
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def chk_diag(nl):
    """R1: MCU-side DIAG_* = U5 pad + 4.7k series; chip-side DIAG_*_Q reaches all three chips."""
    f = []
    for mcu, chip_pin in (("DIAG_EN", "DIAG_EN"), ("DIAG_SEL0", "SEL0"), ("DIAG_SEL1", "SEL1")):
        q = mcu + "_Q"
        pad = MCU_PADS[mcu]
        m = members(nl, mcu)
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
